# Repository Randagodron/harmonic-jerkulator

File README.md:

# harmonic-jerkulator
Fuzz stompbox for electric guitar

This circuit is based on the Harmonic Jerkulator from Tim Escobedo, itself based on the Interfax Harmonic Percolator.

CAD done with KiCAD, simulation done with LTSpice.

Companion article (in french) : http://blog.randagodron.eu/index.php?post/2017/12/23/DIY-audio-Harmonic-Jerkulator

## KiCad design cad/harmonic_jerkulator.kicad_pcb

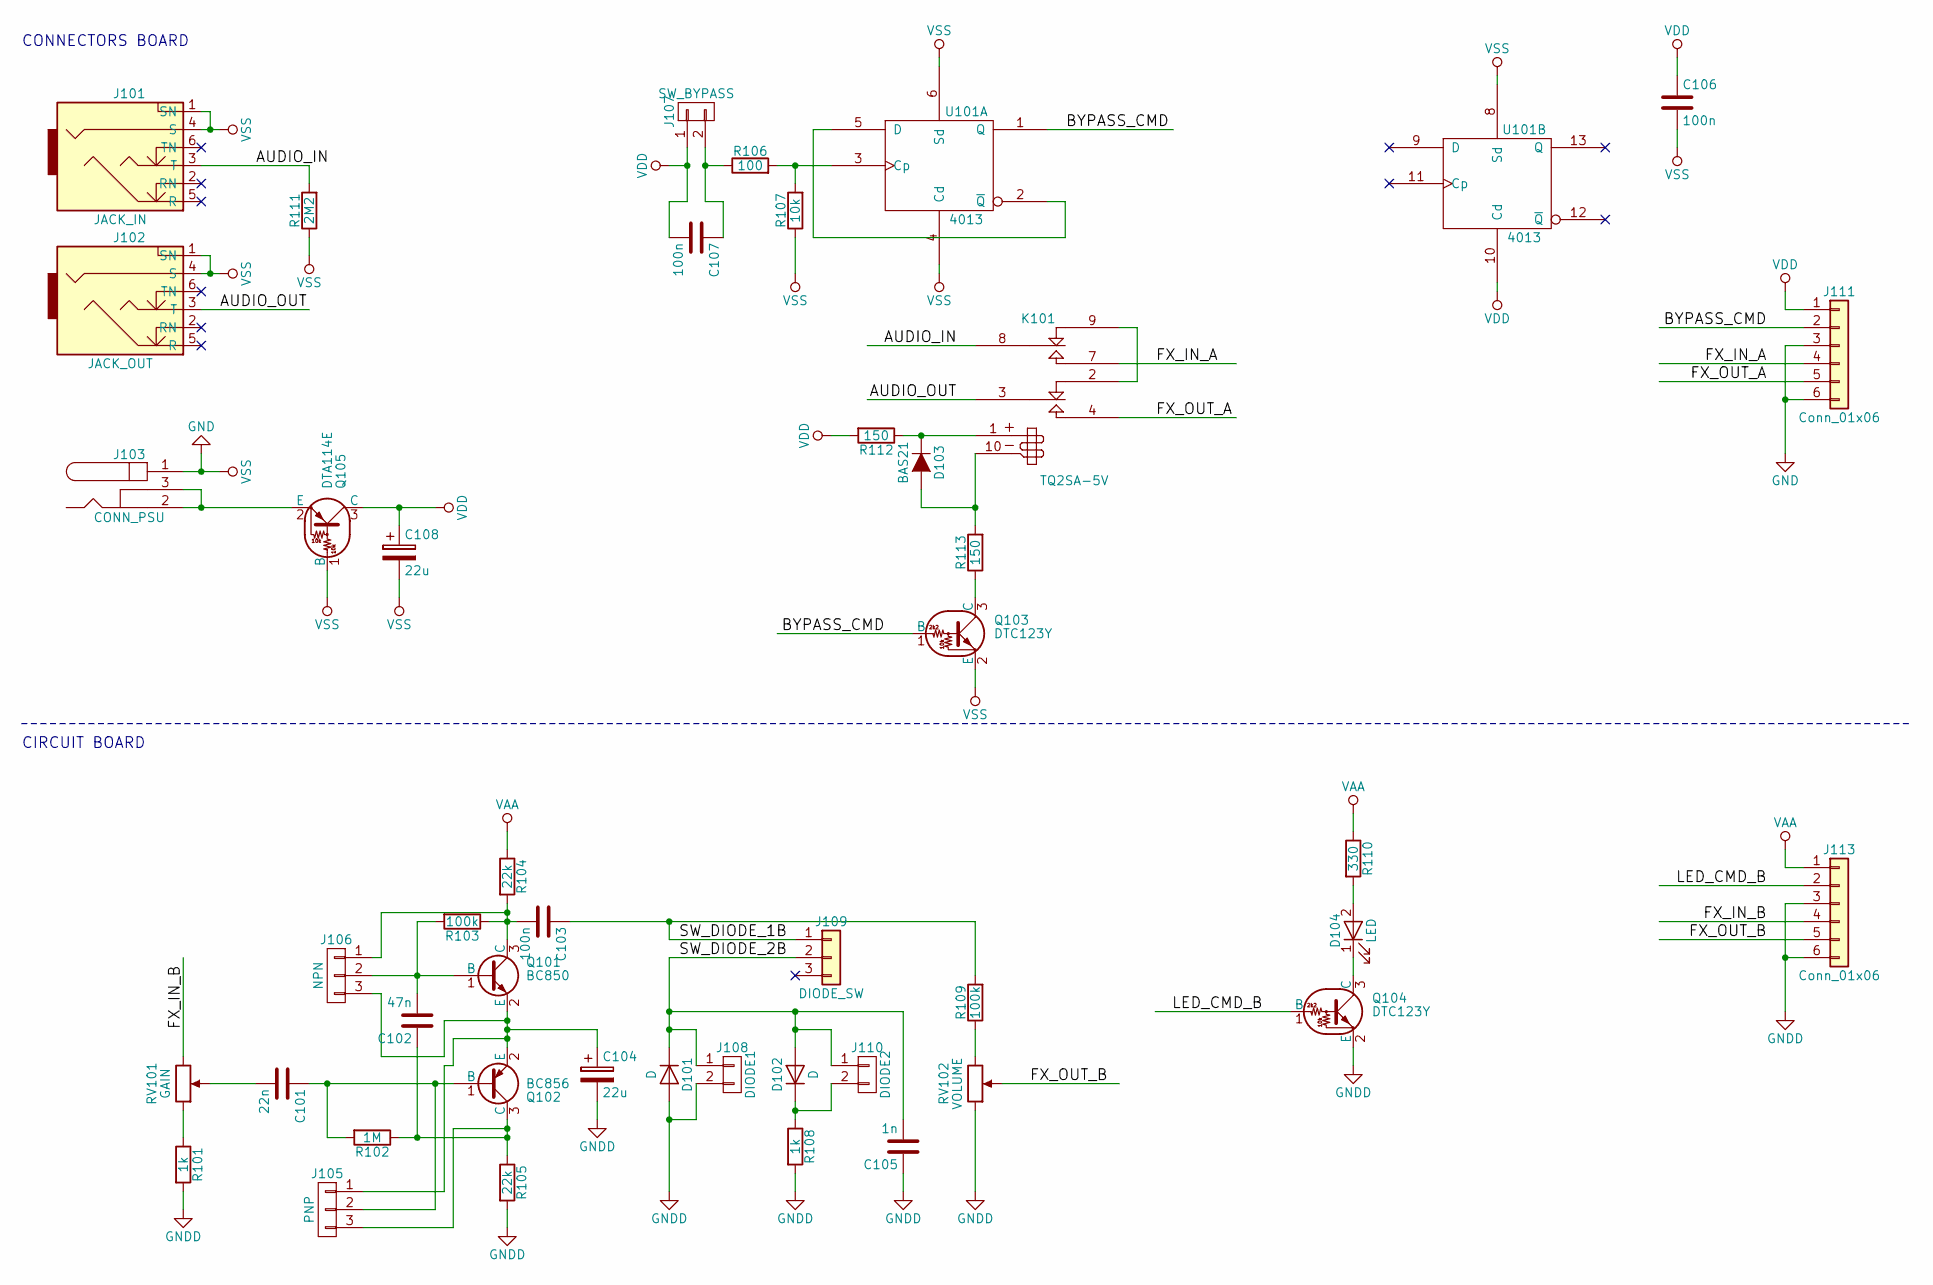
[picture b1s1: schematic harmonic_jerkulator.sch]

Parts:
C101: 22n; C_0603
C102: 47n; C_0603
C103, C106, C107: 100n; C_0603
C104, C108: 22u; CP_Elec_5x5.3
C105: 1n; C_0603
D101, D102: D; SOT-23
D103: BAS21; SOT-23
D104: LED; Pin_Header_Straight_1x02_Pitch2.54mm
J101: JACK_IN; CLIFF_FCR5005x
J102: JACK_OUT; CLIFF_FCR5005x
J103: CONN_PSU; JACK_ALIM
J105: PNP; Pin_Header_Straight_1x03_Pitch2.54mm
J106: NPN; Pin_Header_Straight_1x03_Pitch2.54mm
J107: SW_BYPASS; Pin_Header_Straight_1x02_Pitch2.54mm
J108: DIODE1; Pin_Header_Straight_1x02_Pitch2.54mm
J109: DIODE_SW; Pin_Header_Straight_1x03_Pitch2.54mm
J110: DIODE2; Pin_Header_Straight_1x02_Pitch2.54mm
J111, J113: Conn_01x06; Pin_Header_Straight_1x06_Pitch2.54mm
K101: TQ2SA-5V; TQ2SA
Q101: BC850; SOT-23
Q102: BC856; SOT-23
Q103, Q104: DTC123Y; SOT-23
Q105: DTA114E; SOT-23
R101, R108: 1k; R_0603
R102: 1M; R_0603
R103, R109: 100k; R_0603
R104, R105: 22k; R_0603
R106: 100; R_0603
R107: 10k; R_0603
R110: 330; R_0805
R111: 2M2; R_0603
R112, R113: 150; R_0805
RV101: GAIN; ALPS_RK09L
RV102: VOLUME; ALPS_RK09L
U101: 4013; SOIC-14_N

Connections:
/AUDIO_IN: J101.3 (T), K101.8 (C2), R111.2
/AUDIO_OUT: J102.3 (T), K101.3 (C1)
/BYPASS_CMD: J111.2, Q103.1 (B), U101.1 (Q)
/FX_IN_A: J111.4, K101.7 (T2)
/FX_IN_B: J113.4, RV101.3
/FX_OUT_A: J111.5, K101.4 (T1)
/FX_OUT_B: J113.5, RV102.2
/LED_CMD_B: J113.2, Q104.1 (B)
/SW_DIODE_1B: C103.1, J109.1, R109.2
/SW_DIODE_2B: C105.2, D101.1 (K), D102.2 (A), J108.1, J109.2, J110.1
GND: C106.2, C108.2, J101.1 (SN), J101.4 (S), J102.1 (SN), J102.4 (S), J103.1, J111.3, J111.6, Q103.2 (E), Q105.1 (B), R107.1, R111.1, U101.4 (Cd), U101.6 (Sd), U101.7 (VSS), U101.8 (Sd)
GNDD: C104.2, C105.1, D101.2 (A), J108.2, J113.3, J113.6, Q104.2 (E), R101.2, R105.2, R108.2, RV102.1
unnamed: C101.1, J105.2, Q102.1 (B), R102.2
unnamed: C101.2, RV101.2
unnamed: C102.1, J105.3, Q102.3 (C), R102.1, R105.1
unnamed: C102.2, J106.2, Q101.1 (B), R103.2
unnamed: C103.2, J106.1, Q101.3 (C), R103.1, R104.2
unnamed: C104.1, J105.1, J106.3, Q101.2 (E), Q102.2 (E)
unnamed: C107.1, J107.2, R106.1
unnamed: D102.1 (K), J110.2, R108.1
unnamed: D103.1 (A), K101.10 (-), R113.2
unnamed: D103.3 (K), K101.1 (+), R112.1
unnamed: D104.1 (K), Q104.3 (C)
unnamed: D104.2 (A), R110.2
unnamed: J103.2, J103.3, Q105.2 (E)
unnamed: K101.2 (R1), K101.9 (R2)
unnamed: Q103.3 (C), R113.1
unnamed: R101.1, RV101.1
unnamed: R106.2, R107.2, U101.3 (Cp)
unnamed: R109.1, RV102.3
unnamed: U101.2 (~Q), U101.5 (D)
VAA: J113.1, R104.1, R110.1
VDD: C106.1, C107.2, C108.1, J107.1, J111.1, Q105.3 (C), R112.2, U101.10 (Cd), U101.14 (VDD)

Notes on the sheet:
CONNECTORS BOARD
CIRCUIT BOARD

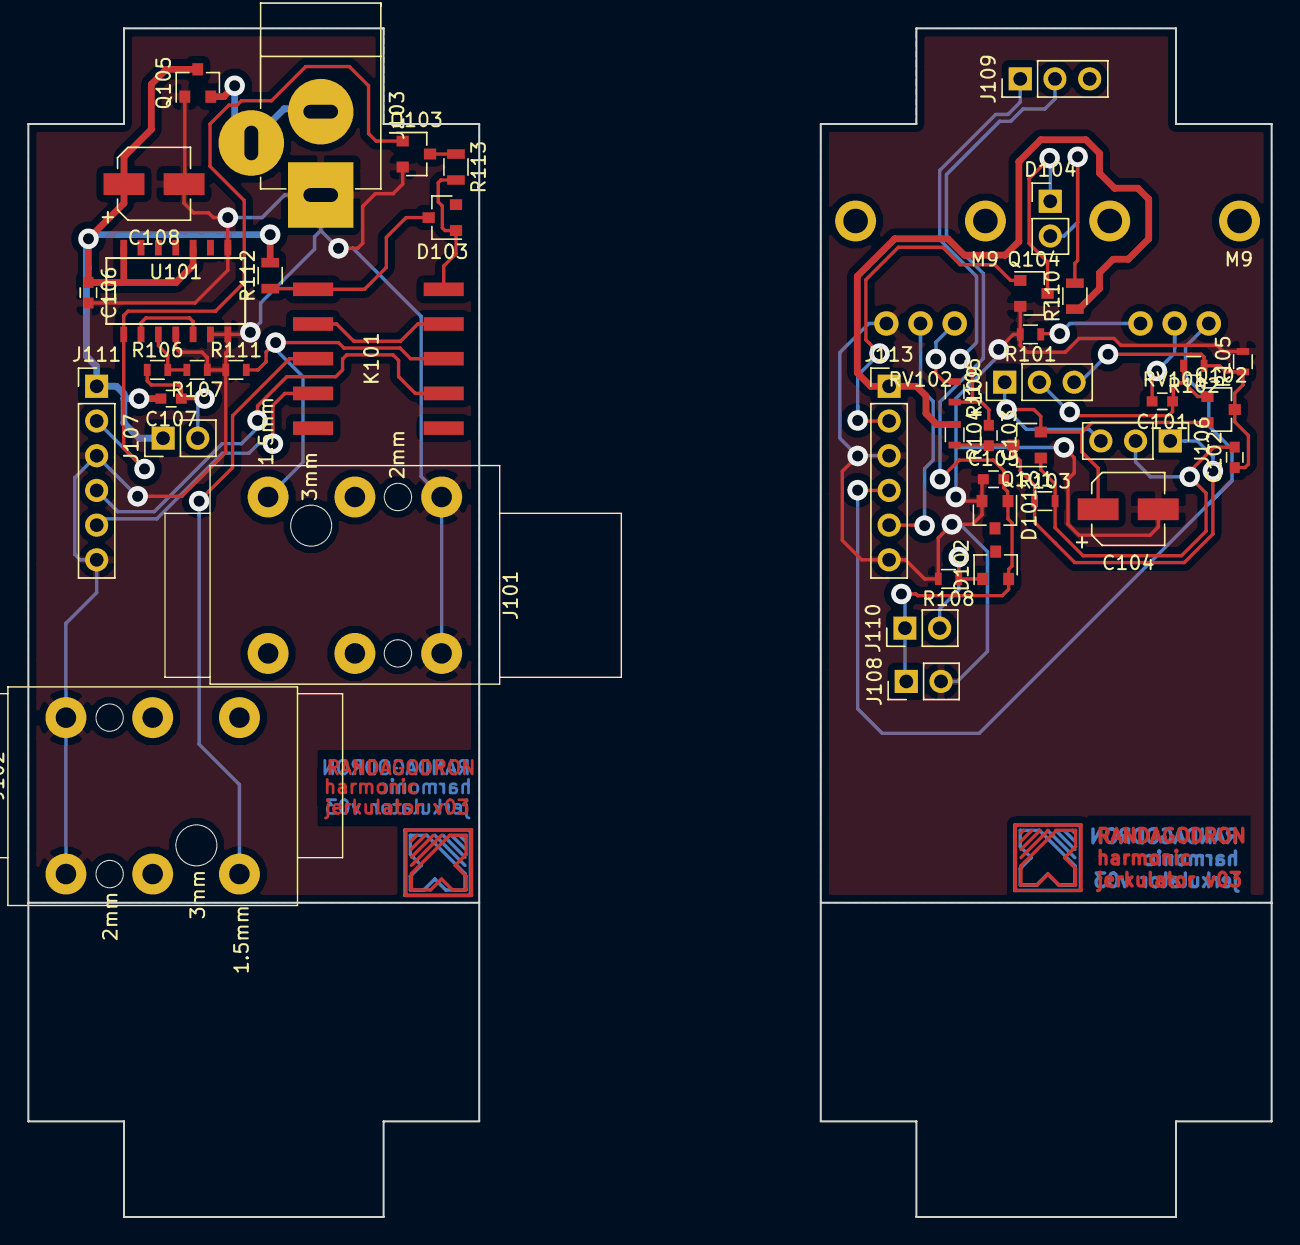
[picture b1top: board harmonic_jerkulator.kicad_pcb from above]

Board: 2 copper layers, 91.0 x 87.0 mm, 45 parts (0 on the bottom side), 33 nets.

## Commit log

2017-08-27 Checked mechanics.
    Components placed.
2017-08-29 Corrected schematic : serial resistors on relay coil. Started layout.
2017-08-29 Corrected pots polarity.
    Connected GND and VSS.
    Done single-side layout on Connectors board.
2017-08-31 Finished layout.
2017-12-09 Corrections on layout.
    Exported layout.
2017-12-28 Corrections on schematic. Not finished.
2017-12-28 Done corrections, issues #1 to #6.
2017-12-28 Changed PSU connector. Corrected layout.
2018-02-04 Added recorded samples of the pedal.
2018-03-18 Corrected unconnected net.
2018-04-19 Corrected jacks spacing.
2018-04-19 Exported Gerbers.
2018-04-19 Saved
2018-06-05 Corrected PCB revision number.
2018-07-15 New samples.
    Images of the schematic (LTspice).
2018-07-15 Generated new samples.
    Added schematic and graph images.
2021-01-01 Added gitignore.
